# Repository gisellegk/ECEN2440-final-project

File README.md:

# ECEN2440-final-project

## Setup
### Eagle
Add folder to project folders: `Options>Directories>Projects`: Add a semicolon after the default / whatever's in there already, then add `<yourfolderpath>\ECEN2440-final-project/PCB`

### CCS
Set workspace to be `<yourfolderpath>\ECEN2440-final-project`. Go to file > import >Code Composer Studio > CCS projects. Hit Browse next to the Select search directory line, and navigate to the ECEN 2440 final project. You should see `rocket-payload-code` show up. Make sure that's checked off, then hit finish.

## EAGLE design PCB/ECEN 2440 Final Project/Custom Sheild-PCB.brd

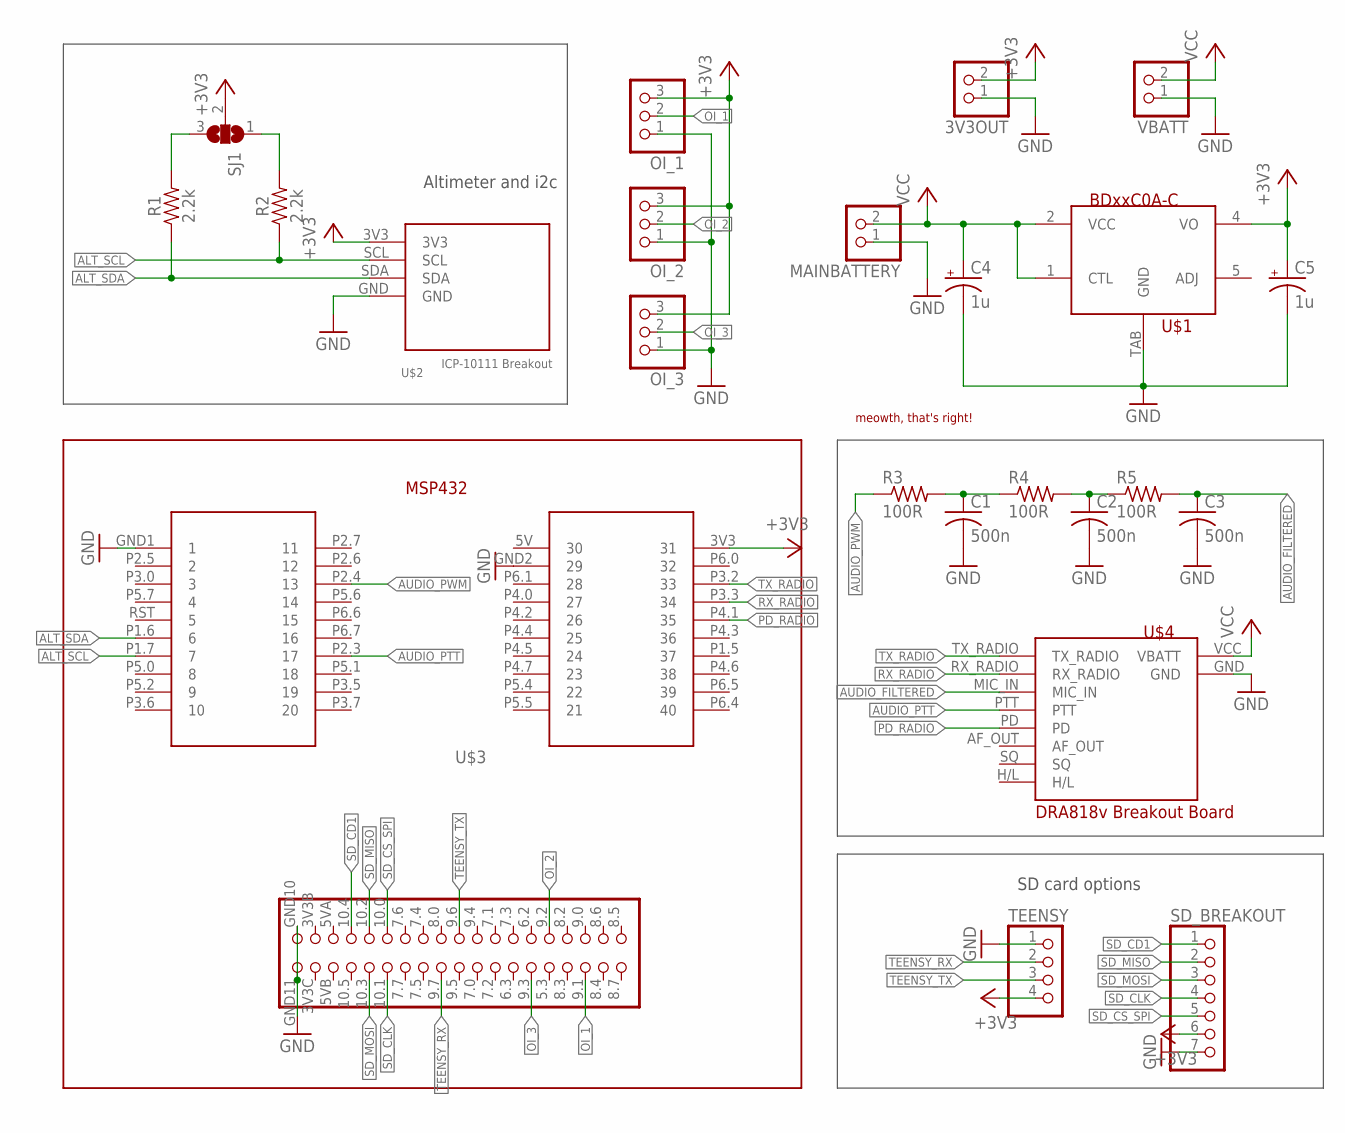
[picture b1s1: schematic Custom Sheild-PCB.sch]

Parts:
3V3OUT: PINHD-1X2; 1X02
C1, C2, C3: 500n; C0805
C4, C5: 1u; PANASONIC_A
MAINBATTERY: PINHD-1X2; 1X02
OI_1, OI_2, OI_3: PINHD-1X3; 1X03
R1, R2: 2.2k; 0603
R3, R4, R5: 100R; R0805
SD_BREAKOUT: PINHD-1X7; 1X07
SJ1: SJ2W; SJ_2
TEENSY: PINHD-1X4; 1X04
U$1: BDXXC0A-CBD33C0AWFP-CE2; TO252-5-11
U$2: ALTIMETER
U$3: MSP432
U$4: DRA_BREAKOUT
U$5: MEOWTH
VBATT: PINHD-1X2; 1X02

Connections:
30: U$3.5V (30)
+3V3: 3V3OUT.2, C5.+, OI_1.3, OI_2.3, OI_3.3, SD_BREAKOUT.6, SJ1.2, TEENSY.4, U$1.4 (VO), U$2.3V3, U$3.3V3 (31)
ALT_SCL: R2.1, U$2.SCL, U$3.P1.7 (7)
ALT_SDA: R1.1, U$2.SDA, U$3.P1.6 (6)
AUDIO_FILTERED: C3.1, R5.2, U$4.MIC_IN
AUDIO_PTT: U$3.P2.3 (17), U$4.PTT
AUDIO_PWM: R3.1, U$3.P2.4 (13)
GND: 3V3OUT.1, C1.2, C2.2, C3.2, C4.-, C5.-, MAINBATTERY.1, OI_1.1, OI_2.1, OI_3.1, SD_BREAKOUT.7, TEENSY.1, U$1.TAB (GND), U$2.GND, U$3.GND1 (1), U$3.GND2 (29), U$3.GND10 (42), U$3.GND11 (41), U$4.GND, VBATT.1
unnamed: R1.2, SJ1.3
unnamed: R2.2, SJ1.1
unnamed: C1.1, R3.2, R4.1
unnamed: C2.1, R4.2, R5.1
OI_1: OI_1.2, U$3.9.1 (73)
OI_2: OI_2.2, U$3.9.2 (70)
OI_3: OI_3.2, U$3.9.3 (67)
PD_RADIO: U$3.P4.1 (35), U$4.PD
RX_RADIO: U$3.P3.3 (34), U$4.RX_RADIO
SD_CD1: SD_BREAKOUT.1, U$3.10.4 (48)
SD_CLK: SD_BREAKOUT.4, U$3.10.1 (51)
SD_CS_SPI: SD_BREAKOUT.5, U$3.10.0 (52)
SD_MISO: SD_BREAKOUT.2, U$3.10.2 (50)
SD_MOSI: SD_BREAKOUT.3, U$3.10.3 (49)
TEENSY_RX: TEENSY.2, U$3.9.7 (57)
TEENSY_TX: TEENSY.3, U$3.9.6 (60)
TX_RADIO: U$3.P3.2 (33), U$4.TX_RADIO
VCC: C4.+, MAINBATTERY.2, U$1.1 (CTL), U$1.2 (VCC), U$4.VCC (VBATT), VBATT.2

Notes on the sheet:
Altimeter and i2c
SD card options

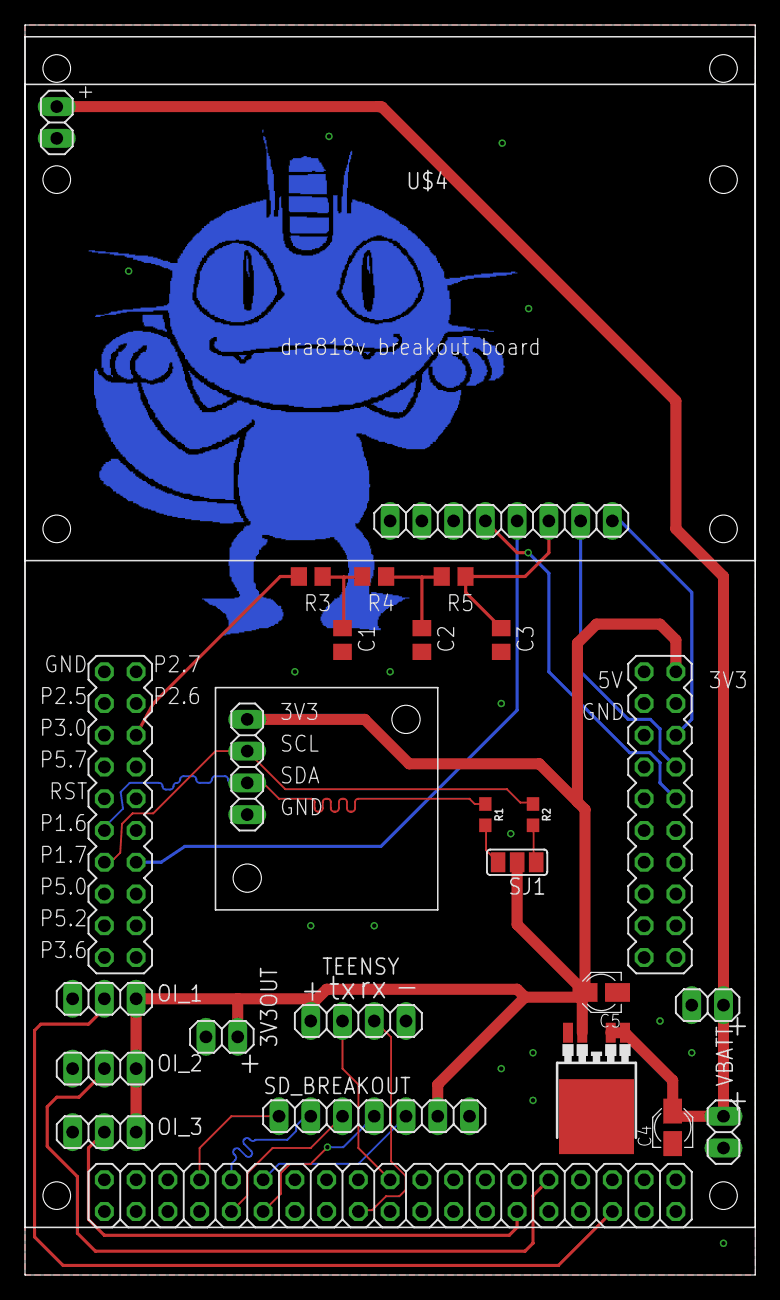
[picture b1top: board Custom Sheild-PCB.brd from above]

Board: 2 copper layers, 58.4 x 100.0 mm, 24 parts (1 on the bottom side), 25 nets.

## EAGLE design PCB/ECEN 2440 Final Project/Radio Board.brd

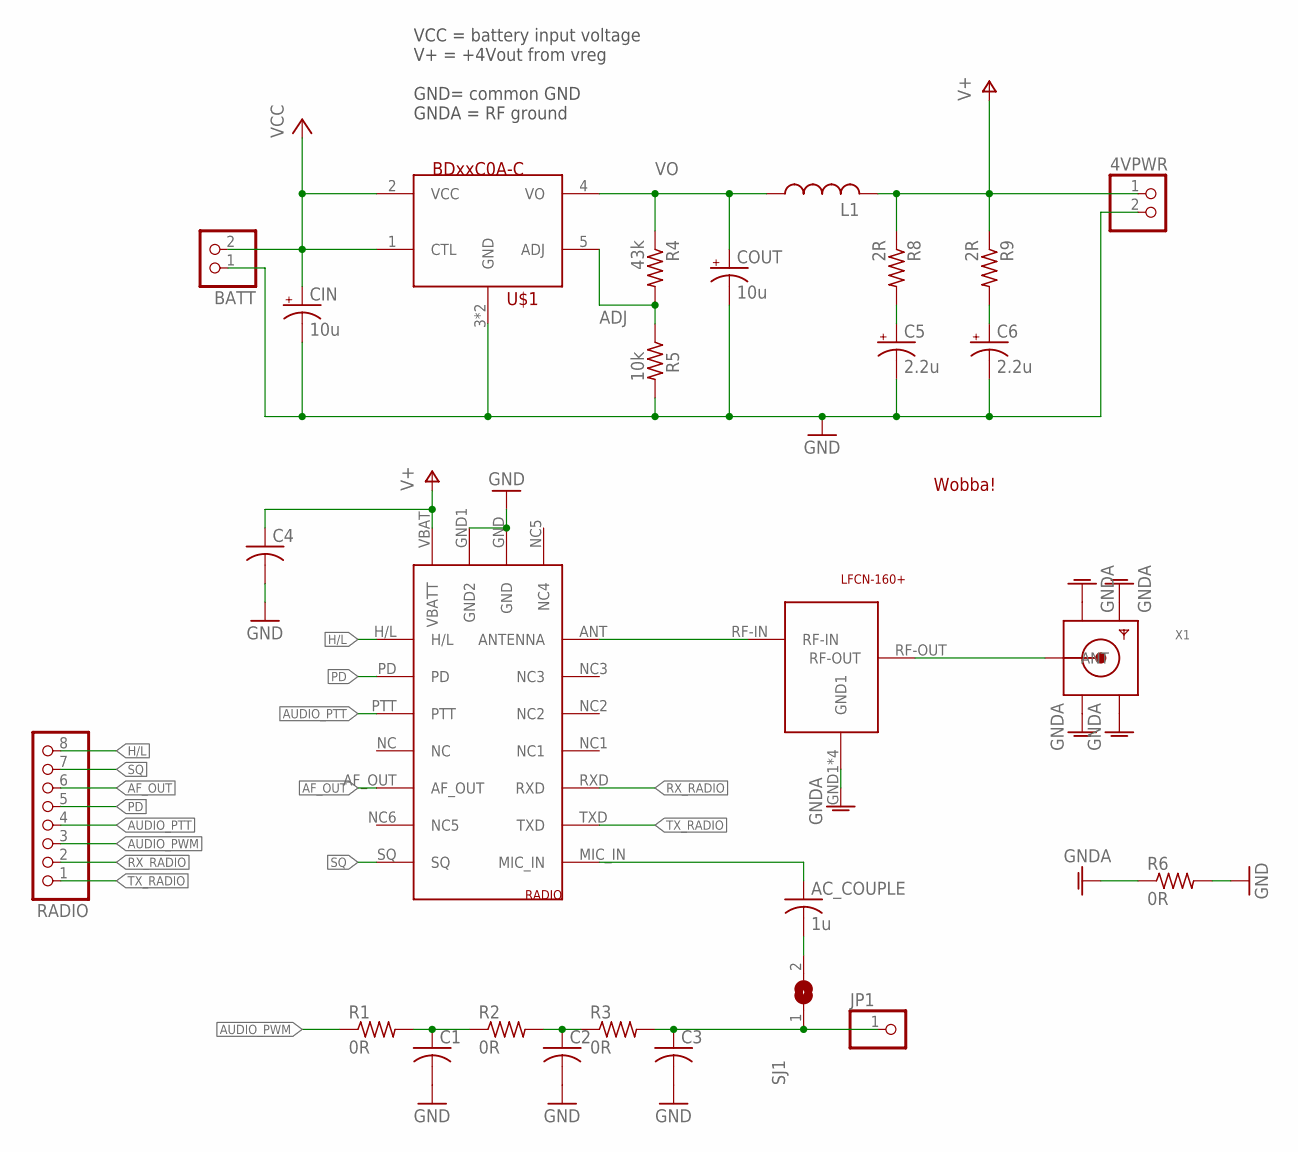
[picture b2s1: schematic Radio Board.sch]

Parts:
4VPWR: PINHD-1X2; 1X02
AC_COUPLE: 1u; C0805
BATT: PINHD-1X2; 1X02
C1, C2, C3: C-USC0805; C0805
C4: 100n; C0805
C5, C6: 2.2u; PANASONIC_A
CIN: 10u; PANASONIC_A
COUT: 10u; PANASONIC_A
JP1: PINHD-1X1; 1X01
L1: L-USL3225M; L3225M
R1, R2, R3, R6: 0R; R0805
R4: 43k; R0805
R5: 10k; R0805
R8, R9: 2R; R0805
RADIO: PINHD-1X8; 1X08
SJ1: SJ
U$1: BDXXC0A-CBD00C0AWHFP-CTR; HRP5
U$2: WOBBUFFET
U$4: RADIO
U$6: LFCN-160+
X1: SMACONNECTOR_EDGE; SMA_EDGELAUNCH

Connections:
ADJ: R4.2, R5.1, U$1.5 (ADJ)
AF_OUT: RADIO.6, U$4.AF_OUT
AUDIO_PTT: RADIO.4, U$4.PTT
AUDIO_PWM: R1.1, RADIO.3
GND: 4VPWR.2, BATT.1, C1.2, C2.2, C3.2, C4.2, C5.-, C6.-, CIN.-, COUT.-, R5.2, R6.2, U$1.3 (GND), U$1.6 (GND), U$4.GND, U$4.GND1 (GND2)
GNDA: R6.1, U$6.GND1, U$6.GND2 (GND1), U$6.P$1 (GND1), U$6.P$2 (GND1), X1.GND@1 (GND4), X1.GND@2 (GND3), X1.GND@3 (GND2), X1.GND@4 (GND1)
H/L: RADIO.8, U$4.H/L
unnamed: U$4.ANT (ANTENNA), U$6.RF-IN
unnamed: C1.1, R1.2, R2.1
unnamed: C3.1, JP1.1, R3.2, SJ1.1
unnamed: C2.1, R2.2, R3.1
unnamed: AC_COUPLE.1, U$4.MIC_IN
unnamed: U$6.RF-OUT, X1.P (ANT)
unnamed: AC_COUPLE.2, SJ1.2
unnamed: C6.+, R9.2
unnamed: C5.+, R8.2
PD: RADIO.5, U$4.PD
RX_RADIO: RADIO.2, U$4.RXD
SQ: RADIO.7, U$4.SQ
TX_RADIO: RADIO.1, U$4.TXD
V+: 4VPWR.1, C4.1, L1.2, R8.1, R9.1, U$4.VBAT (VBATT)
VCC: BATT.2, CIN.+, U$1.1 (CTL), U$1.2 (VCC)
VO: COUT.+, L1.1, R4.1, U$1.4 (VO)

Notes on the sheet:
VCC = battery input voltage V+ = +4Vout from vreg GND= common GND GNDA = RF ground

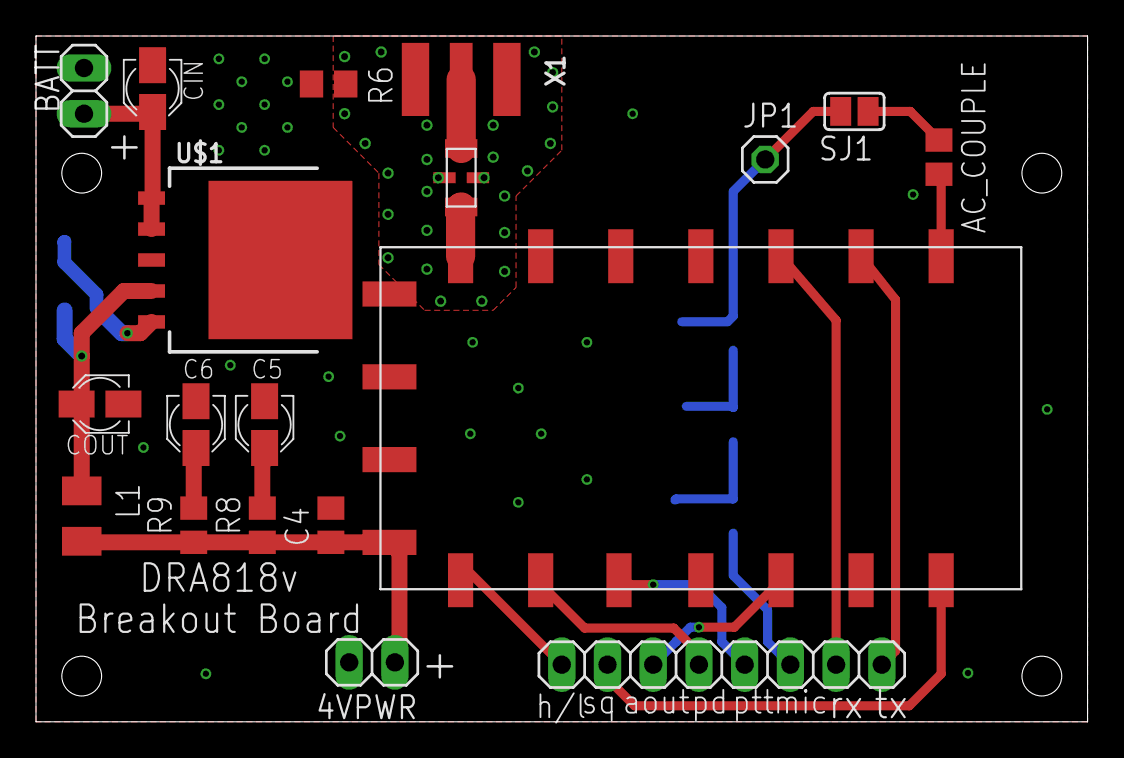
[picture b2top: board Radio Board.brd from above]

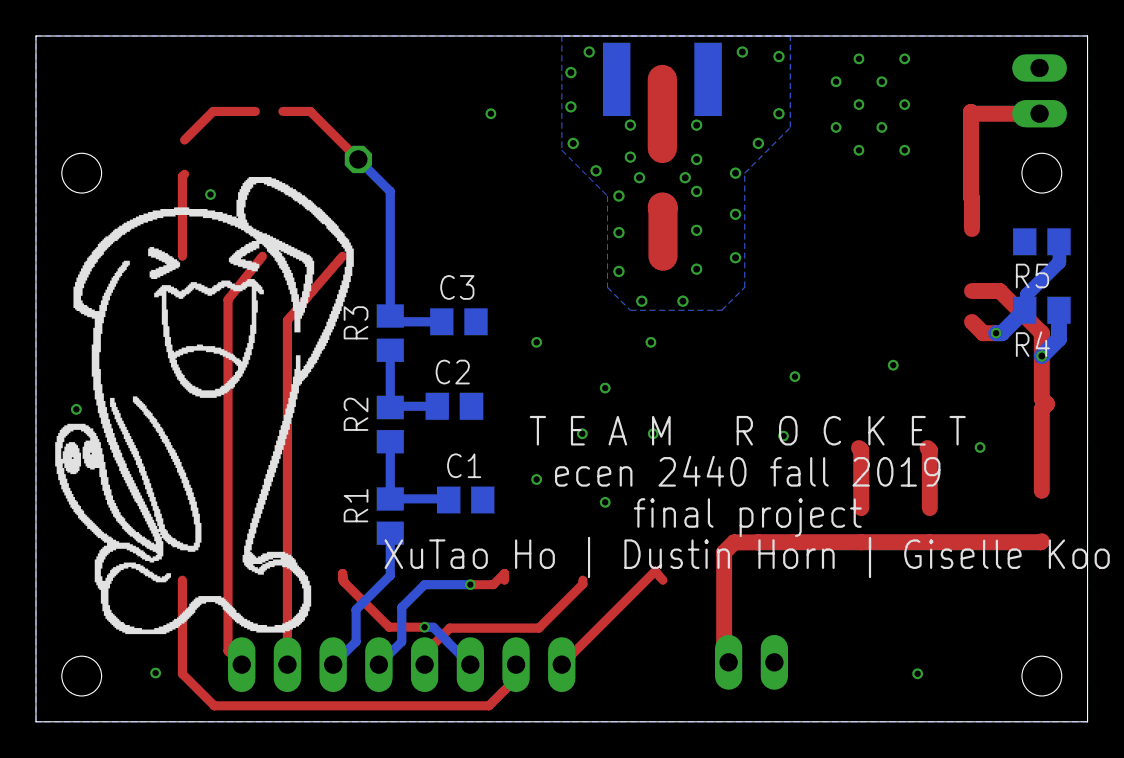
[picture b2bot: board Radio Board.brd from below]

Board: 2 copper layers, 58.4 x 38.1 mm, 28 parts (9 on the bottom side), 23 nets.

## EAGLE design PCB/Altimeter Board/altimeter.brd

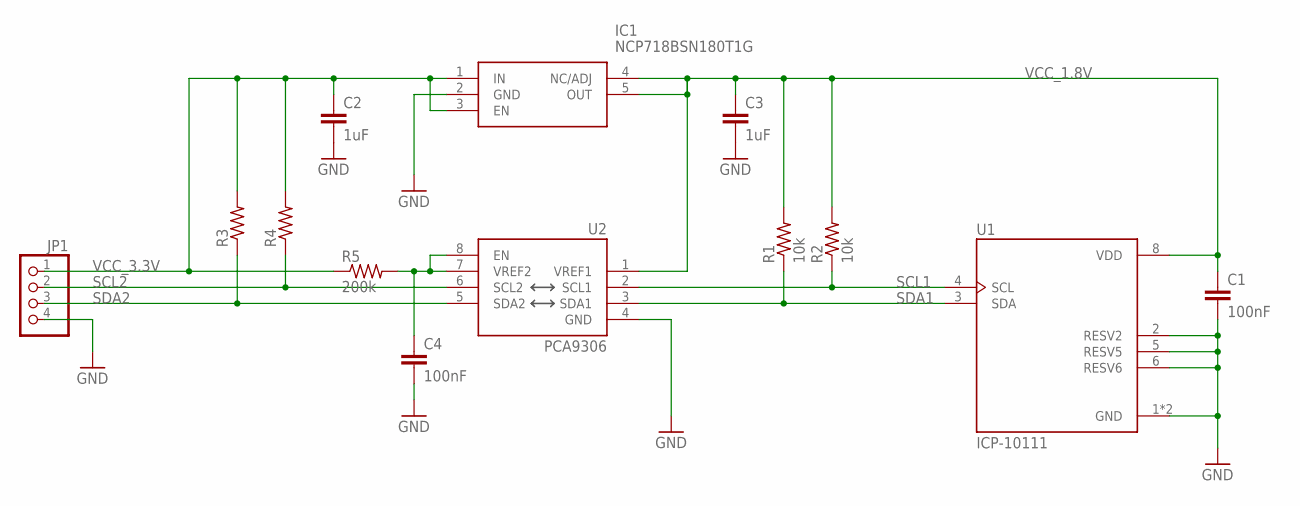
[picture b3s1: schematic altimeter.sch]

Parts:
C1, C4: 100nF; C0402
C2, C3: 1uF; C0402
IC1: NCP718BSN180T1G; SOT95P280X100-5N
JP1: PINHD-1X4; 1X04
R1, R2: 10k; R0402
R3, R4: R-US_R0402; R0402
R5: 200k; R0402
U1: ICP-10111; PSON65P250X200X100-8N
U2: PCA9306; PCA9306DC

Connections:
GND: C1.2, C2.2, C3.2, C4.2, IC1.2 (GND), JP1.4, U1.1 (GND), U1.2 (RESV2), U1.5 (RESV5), U1.6 (RESV6), U1.7 (GND), U2.4 (GND)
unnamed: C4.1, R5.2, U2.7 (VREF2), U2.8 (EN)
SCL1: R2.1, U1.4 (SCL), U2.2 (SCL1)
SCL2: JP1.2, R4.1, U2.6 (SCL2)
SDA1: R1.1, U1.3 (SDA), U2.3 (SDA1)
SDA2: JP1.3, R3.1, U2.5 (SDA2)
VCC_1.8V: C1.1, C3.1, IC1.4 (NC/ADJ), IC1.5 (OUT), R1.2, R2.2, U1.8 (VDD), U2.1 (VREF1)
VCC_3.3V: C2.1, IC1.1 (IN), IC1.3 (EN), JP1.1, R3.2, R4.2, R5.1

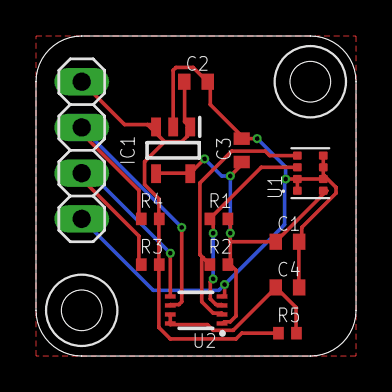
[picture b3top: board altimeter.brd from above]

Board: 2 copper layers, 17.8 x 17.8 mm, 15 parts (0 on the bottom side), 8 nets.

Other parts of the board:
U$1, U$2: #2

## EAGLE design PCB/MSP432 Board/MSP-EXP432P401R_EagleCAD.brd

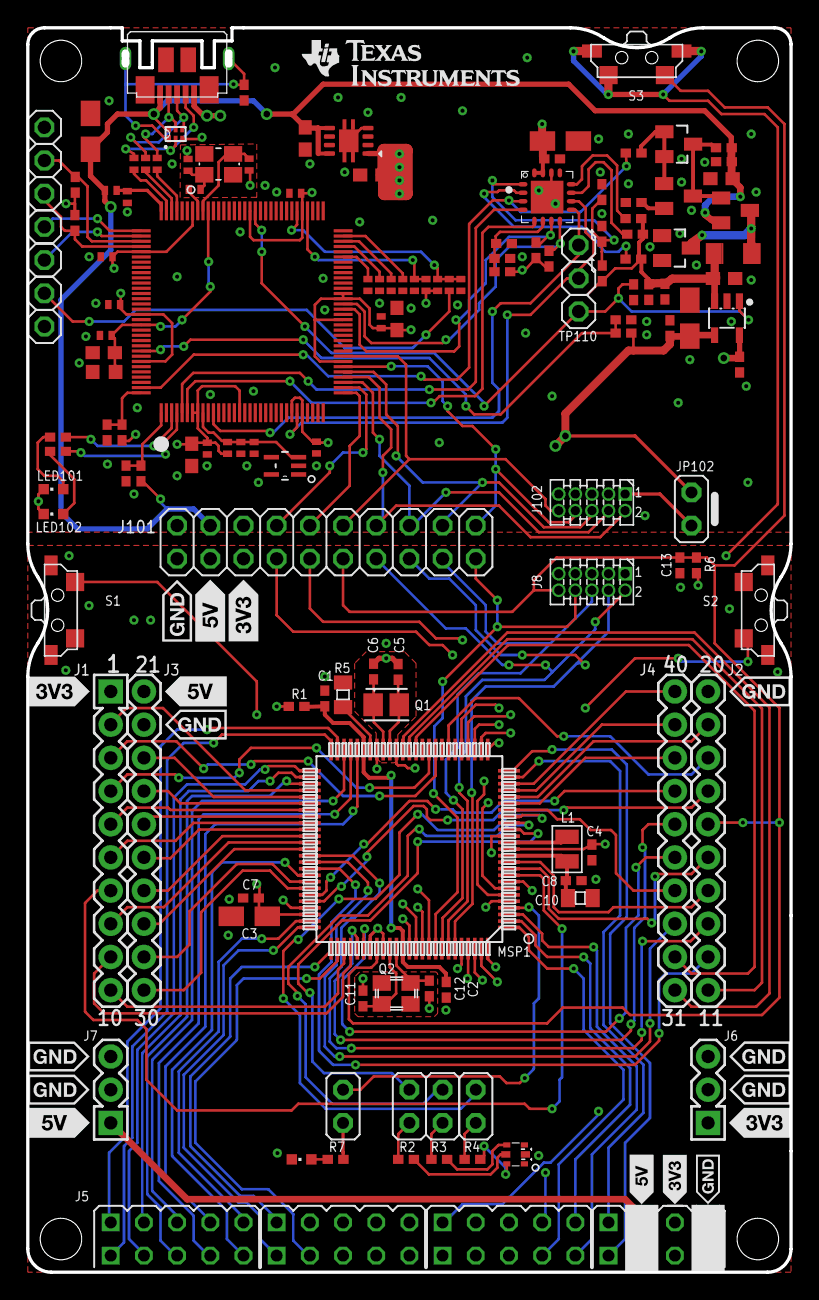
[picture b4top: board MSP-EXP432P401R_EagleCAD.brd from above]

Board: 4 copper layers, 58.1 x 94.9 mm, 150 parts (0 on the bottom side), 160 nets.

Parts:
C1, C2, C4, C7, C8, C118, C120, C124, C129: 100n; 0402
C3: 10u; A/3216-18R
C5, C6, C11, C12: 22p; 0402
C10: 4u7; CSMD0805
C13: 1n; 0402
C101, C102: 12pF; C0402
C103, C131, C150: 0.1uF; C0402
C104, C110, C112, C114, C123: 10n; C0402
C105: 2u2; C0603
C106, C140: 4.7u; A/3216-18R
C107, C130, C132, C141: 1u; C0603
C108: DNP; C0402
C111, C113, C121: 100n; C0402
C115, C116: 33p; 0402
C117, C119: 4.7u; C0603
C126, C127: 220n; 0402
C128: 47u; A/3216-18R
C133: 2.2uF; C0603K
D101, D102: BAS40-05; SOT23
IC101: TPS73533DRB; SON8
IC102: TPD4E004_DRY_6; DRY6
IC103: TPS2102DBV; SOT23-5
IC106: TM4C129ENCPDT; TQFP-128
IC107: LM4040B25_DCK_5; DCK5
J1: J1
J2: J2
J3: J3
J4: J4
J5: EDGE_CON; BOTTOM_CONNECTOR
J6: HEADER 1X03; 3PIN_PWR_3V3
J7: BP_HEADERS_PWR_5V; 3PIN_PWR_5V
J8, J102: ARM-10
J101: J101_432
JP8: LED1; JP1M
JP9: LED2_RED; JP1M
JP10: LED2_GREEN; JP1M
JP11: LED2_BLUE; JP1M
JP102: JP1M
L1: 4.7uH; 0806
L101: 2u2; L3216C
LED1, LED101, LED102: CHIPLED_0603
LED2: EVERLIGHT_19-337; RGB_LED
MSP1: MSP432; PZ100
MSP101: MSP430G2452IRSA16R; RSA16
Q1: LF_XTAL
Q2: FA-238
Q101: NX3225GA_OSC; NX3225GA
R1: 0R; 0402
R2: 110R; 0402
R3: 16R; 0402
R4: 24R; 0402
R5: 91kOhm, 0.1%, 25ppm/C; 0805
R6, R107: 47k; 0402
R7, R111, R120, R124: 470; 0402
R101, R134: DNP; 0402
R102: 100; R0402
R103: 10k; R0402
R104, R140: 51; R0402
R105: 1k 1%; R0402
R106: 2R; R0402
R108, R109, R110: 1k; R0402
R112, R113, R114, R115, R133, R135, R136: 220k; 0402
R116, R117: 4k7; 0402
R118: 820; 0402
R119: 0; 0402
R123: 33; 0402
R125, R129: 10k; 0402
R126: 2k2; 0402
R127: 3k3; 0402
R128: 6k8; 0402
R131, R137, R138: 0; R0402
R132: 330k; 0402
R139: dnp; R0402
S1, S2, S3: TS-1188E
T101: DMG1013UW; SOT23
T102: BC850CW-115; SOT23-BEC
TP101, TP102, TP103, TP104, TP105, TP106, TP107, TP108, TP109, TP110: TEST_PIN2; 1X01
U$1, U$2, U$3, U$5: MOUNTHOLE_125MIL
U$4: LOGO16_TPLACE
U$7: MIKE_TM
U$8: P401R_REARSILK_REV2_1
U$9: REAR_TILOGO
U$10: COMPLIANCE_SUITESYMBOLONLY; EVM_COMPLIANCESUITE_SYMBOLONLY
U$11: COMPLIANCE_FCC_TEXTREAR; COMPLIANCE_FCC_TEXT
U$12: LOGO-ROCKET
U$13: P401R_SILKLABEL; SILKLABELUPDATED
USB101: MOLEX_105164-0001

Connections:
!RST: C13.1, J2.16, J8.10, J101.11, MSP1.83, R6.1, S3.S1
+3V3: C3.+, C4.1, C7.1, J1.1, J5.35, J5.36, J6.1, J8.1, J101.5, MSP1.13, MSP1.73, R1.1, R6.2
+5V: J3.21, J5.33, J5.34, J7.1, J101.3
AVCC: C116.2, MSP101.6, R114.2, R115.1
AVCCOUT: C115.2, MSP101.1, R112.2, R113.1
DCDCCAL0: MSP101.12, R126.2
DCDCCAL1: MSP101.2, R127.2
DCDCCAL2: MSP101.11, R128.2
DCDCIO0: IC106.P$5, MSP101.4
DCDCIO1: IC106.P$6, MSP101.5
DCDCPULSE: IC106.P$127, MSP101.3, R118.2
DCDCRST: IC106.P$11, MSP101.9, TP108.1
DCDCTEST: IC106.P$27, MSP101.10, TP109.1
DCOR: MSP1.44, R5.1
HOSTSCL: IC106.P$49, MSP101.7, R117.2
HOSTSDA: IC106.P$50, MSP101.8, R116.2
IRSTN: R102.1, TP106.1
ITCK: IC106.P$100, R129.1, TP103.1
ITDI: IC106.P$98, TP105.1
ITDO: IC106.P$97, TP104.1
ITMS: IC106.P$99, R125.1, TP102.1
LED0: IC106.P$3, R111.1
LED1: IC106.P$4, R124.1
unnamed: J102.1, JP102.2
unnamed: IC106.P$63, R108.2
unnamed: LED102.A, R124.2
unnamed: C1.1, C2.1, MSP1.45, MSP1.87, R1.2
unnamed: LED101.A, R111.2
unnamed: JP9.2, R2.1
unnamed: LED2.5, R2.2
unnamed: LED2.6, R3.2
unnamed: LED2.4, R4.2
unnamed: R119.1, T102.E
unnamed: D101.1, D101.2, R118.1, T102.B
unnamed: D102.3, L101.1, T101.3
unnamed: D101.3, R120.2, T101.1, T102.C
unnamed: LED1.A, R7.2
unnamed: JP10.2, R3.1
unnamed: IC106.P$93, R138.2
unnamed: IC106.P$61, R110.2
unnamed: IC106.P$95, R131.2
unnamed: JP11.2, R4.1
unnamed: IC106.P$62, R109.2
unnamed: JP8.2, R7.1
unnamed: C6.1, MSP1.42, Q1.1
unnamed: C5.1, MSP1.41, Q1.2
unnamed: IC106.P$59, R139.2
OSC0: C102.1, IC106.P$88, Q101.3
OSC1: IC106.P$89, R106.2
OSC1_R: C101.1, Q101.1, R106.1
P1.0_LED1: JP8.1, MSP1.4
P1.1_BUTTON1: MSP1.5, S1.S1
P1.2_BCLUART_RXD: J101.7, MSP1.6
P1.3_BCLUART_TXD: J101.9, MSP1.7
P1.4_BUTTON2: MSP1.8, S2.S1
P1.5_SPICLK_J1.7: J1.7, MSP1.9
P1.6_SPIMOSI_J2.15: J2.15, MSP1.10
P1.7_SPIMISO_J2.14: J2.14, MSP1.11
P2.0_RGBLED_RED: JP9.1, MSP1.16
P2.1_RGBLED_GREEN: JP10.1, MSP1.17
P2.2_RGBLED_BLUE: JP11.1, MSP1.18
P2.3_IO_J4.34: J4.34, MSP1.19
P2.4_PWM_J4.38: J4.38, MSP1.20
P2.5_PWM_J2.19: J2.19, MSP1.21
P2.6_PWM_J4.39: J4.39, MSP1.22
P2.7_PWM_J4.40: J4.40, MSP1.23
P3.0_IO_J2.18: J2.18, MSP1.32
P3.2_URXD_J1.3: J1.3, MSP1.34
P3.3_UTXD_J1.4: J1.4, MSP1.35
P3.5_IO_J4.32: J4.32, MSP1.37
P3.6_IO_J2.11: J2.11, MSP1.38
P3.7_IO_J4.31: J4.31, MSP1.39
P4.0_A13_J3.24: J3.24, MSP1.56
P4.1_IO_J1.5: J1.5, MSP1.57
P4.2_A11_J3.25: J3.25, MSP1.58
P4.3_A10_J1.6: J1.6, MSP1.59
P4.4_A9_J3.26: J3.26, MSP1.60
P4.5_A8_J3.27: J3.27, MSP1.61
P4.6_IO_J1.8: J1.8, MSP1.62
P4.7_A6_J3.28: J3.28, MSP1.63
P5.0_IO_J2.13: J2.13, MSP1.64
P5.1_IO_J4.33: J4.33, MSP1.65
P5.2/XT2IN: C12.1, MSP1.86, Q2.1
P5.2_IO_J2.12: J2.12, MSP1.66
P5.3: J5.9, MSP1.67
P5.3/XT2OUT: C11.1, MSP1.85, Q2.3
P5.4_IO_J3.29: J3.29, MSP1.68
P5.5_IO_J3.30: J3.30, MSP1.69
P5.6_PWM_J4.37: J4.37, MSP1.70
P5.7_IO_J2.17: J2.17, MSP1.71
P6.0_A15_J1.2: J1.2, MSP1.54
P6.1_A14_J3.23: J3.23, MSP1.55
P6.2: J5.12, MSP1.76
P6.3: J5.13, MSP1.77
P6.4_I2CSDA_J1.10: J1.10, MSP1.78
P6.5_I2CSCL_J1.9: J1.9, MSP1.79
P6.6_CAPTURE_J4.36: J4.36, MSP1.80
P6.7_CAPTURE_J4.35: J4.35, MSP1.81
P7.0: J5.17, MSP1.88
P7.1: J5.16, MSP1.89
P7.2: J5.15, MSP1.90
P7.3: J5.14, MSP1.91
P7.4: J5.24, MSP1.26
P7.5: J5.23, MSP1.27
P7.6: J5.26, MSP1.28
P7.7: J5.25, MSP1.29
P8.0: J5.22, MSP1.30
P8.2: J5.8, MSP1.46
P8.3: J5.7, MSP1.47
P8.4: J5.6, MSP1.48
P8.5: J5.2, MSP1.49
P8.6: J5.1, MSP1.50
P8.7: J5.3, MSP1.51
P9.0: J5.4, MSP1.52
P9.1: J5.5, MSP1.53
P9.2: J5.10, MSP1.74
P9.3: J5.11, MSP1.75
P9.4: J5.18, MSP1.96
P9.5: J5.19, MSP1.97
P9.6: J5.20, MSP1.98
P9.7: J5.21, MSP1.99
P10.0: J5.28, MSP1.100
P10.1: J5.27, MSP1.1
P10.2: J5.30, MSP1.2
P10.3: J5.29, MSP1.3
P10.4: J5.32, MSP1.24
P10.5: J5.31, MSP1.25
P96VBUS: C150.1, IC106.P$96, R140.2
REF_MAIN_LDO: IC106.P$128, R135.2, R136.2
REF_TARGET_VCC: IC106.P$120, R101.2, R134.2
TCK_SWDCLK: J8.4, J101.15, MSP1.95
TDI: J8.8, J101.19, MSP1.92
TDO_SWO: J8.6, J101.17, MSP1.93
TMS_SWDIO: J8.2, J101.13, MSP1.94
VBUS_DETECT: IC106.P$1, R132.2, R133.2
VCCEN1: IC103.1, IC106.P$78, R107.1, TP110.1
VCORE: C8.1, C10.1, L1.1, MSP1.12
VDDC: C131.1, C132.2, C133.1, IC106.P$87, IC106.P$115
VREFA+: C110.1, C111.1, IC106.P$9, IC107.3, R105.1
VSW: L1.2, MSP1.14
XDS-GND: C1.2, C2.2, C3.-, C4.2, C5.2, C6.2, C7.2, C8.2, C10.2, C11.2, C12.2, C13.2, J2.20, J3.22, J5.37, J5.38, J6.2, J6.3, J7.2, J7.3, J8.3, J8.5, J8.7, J8.9, J101.1, LED1.C, LED2.1, LED2.2, LED2.3, MSP1.15, MSP1.40, MSP1.43, MSP1.72, MSP1.82, MSP1.84, R5.2, S1.G1, S1.G2, S1.S2, S2.G1, S2.G2, S2.S2, S3.G1, S3.G2, S3.S2
XDSET_!RST: C108.1, IC106.P$70, R102.2, R103.2
XDSET_DM: IC102.5, R138.1, USB101.D-
XDSET_DP: IC102.4, R137.1, USB101.D+
XDSET_DPR: IC106.P$94, R137.2
XDSET_GND: C101.2, C102.2, C103.2, C104.2, C105.2, C106.-, C107.2, C108.2, C110.2, C111.2, C112.2, C113.2, C114.2, C115.1, C116.1, C117.2, C118.2, C119.2, C120.2, C121.2, C123.2, C124.2, C126.2, C127.2, C128.-, C129.2, C130.1, C131.2, C132.1, C133.2, C140.-, C141.2, C150.2, D102.1, D102.2, IC101.4, IC101.9, IC102.3, IC103.2, IC106.P$10, IC106.P$17, IC106.P$48, IC106.P$55, IC106.P$58, IC106.P$64, IC106.P$66, IC106.P$80, IC106.P$114, IC107.1, J101.2, J102.3, J102.5, J102.7, J102.9, LED101.C, LED102.C, MSP101.13, MSP101.14, MSP101.TP, R101.1, R107.2, R108.1, R109.1, R110.1, R113.2, R115.2, R119.2, R123.2, R133.1, R136.1, R139.1, TP101.1, USB101.GND
XDSET_ID: IC102.2, R131.1, USB101.ID
XDSET_RESET_OUT: IC106.P$40, J101.12, J102.10
XDSET_RXD: IC106.P$33, J101.10
XDSET_SHIELD: IC102.1, R123.1, USB101.SHIELD_TH1, USB101.SHIELD_TH2
XDSET_TCK_SWDCLK: IC106.P$35, J101.16, J102.4
XDSET_TDI: IC106.P$38, J101.20, J102.8
XDSET_TDO_SWO: IC106.P$37, J101.18, J102.6
XDSET_TMS_SWDIO: IC106.P$36, J101.14, J102.2
XDSET_TXD: IC106.P$34, J101.8
XDSET_VBAT: C103.1, IC106.P$68, R104.2
XDSET_VBUS: C117.1, C118.1, C140.+, C141.1, IC101.5, IC101.8, IC102.6, J101.4, R120.1, R132.1, R140.1, T101.2, USB101.VBUS
XDSET_VCC: C104.1, C105.1, C106.+, C107.1, C112.1, C113.1, C114.1, C121.1, C123.1, C124.1, C126.1, C130.2, IC101.1, IC103.5, IC106.P$7, IC106.P$8, IC106.P$16, IC106.P$26, IC106.P$28, IC106.P$39, IC106.P$47, IC106.P$51, IC106.P$52, IC106.P$69, IC106.P$79, IC106.P$90, IC106.P$101, IC106.P$113, IC106.P$122, MSP101.15, MSP101.16, R103.1, R104.1, R105.2, R114.1, R116.1, R117.1, R125.2, R129.2, R135.1, TP107.1
XDSET_VCCOUT: C119.1, C120.1, C127.1, IC103.3, L101.2, R112.1, R126.1, R127.1, R128.1
XDSET_VCCTARGET: C128.+, C129.1, IC103.4, J101.6, JP102.1, R134.1

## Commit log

2019-10-30 setting up folder structure
2019-10-30 add ccs project folder
2019-10-30 added comment
2019-10-30 add readme with setup instructions for eagle and CCS
2019-10-30 markdown syntax
2019-11-06 final project proposal commit
2019-11-11 Add PCB stuff with components and a couple wiring traces
2019-11-11 add ltspice files and screenshots
2019-11-11 ltspice
2019-11-11 Created Library
2019-11-11 add altimeter board
2019-11-11 Created library and made altimeter
2019-11-12 Made MSP432 and fixed other components
2019-11-13 Added the radio device, and made a couple connections
2019-11-13 Fixed the DRA818 and started connecting traces
2019-11-13 Made changes to the MSP432 and added bottom row
2019-11-13 made a couple connections
2019-11-14 Connected Pins
2019-11-14 add teensy lib
2019-11-14 Work
2019-11-14 PDR schematic and board
2019-11-14 Final board and schematic
2019-11-15 Made updates to board and created now radio breakout board
2019-11-17 add unnecessary files to gitignore
2019-11-17 add some new ltpsice models
2019-11-17 add pcb way quote image
2019-11-17 lt spice stuff
2019-11-17 Revision 1 of Altimeter code
2019-11-18 add preliminary teensy UART stuff
2019-11-18 Altimeter Code Revision 3 (in Altimeter Rev. 2 Folder)
2019-11-18 add uart WIP stuff from lab folder
2019-11-18 minor changes to board
2019-11-18 Board
2019-11-18 move teensy code into code dir
2019-11-18 mod gitignore
2019-11-18 move code into code directory
2019-11-18 New changes to pcb board
2019-11-18 Final updates to the board
2019-11-18 remove files i accidentally forgot to gitignore
2019-11-18 gitignore those files
2019-11-19 add altimeter test code & screenshot
2019-11-19 i forgot it was a git repo inside T_T
2019-11-19 radio board routing
2019-11-19 PWM Code and Computations
2019-11-19 final (before review & order) dra818v breakout board
2019-11-19 prettyfy schematic. vague shield board layout.
2019-11-19 I2C Code for Altimeter
2019-11-20 Changes to board of sheild
2019-11-20 changes to the sheild board
2019-11-20 changes to the traces of the shield board
2019-11-20 changes to the traces of the sheild board
2019-11-20 changes to traces on sheild board
2019-11-22 Created PWM code and did stuff with code
2019-11-22 SPICE models everywhere
2019-11-23 final (i hope) radio board
2019-11-24 final board maybe??
2019-11-24 pspice is terrible
2019-11-24 naming
2019-11-24 add voltage test points
2019-11-24 Fix MSP432 footprint
2019-11-25 really important commit
2019-11-25 idk what i changed lol
2019-11-27 UART echoing works
2019-11-27 update gitignore to reflect new file structure.
2019-11-27 i wonder if we should just gitignore the .epf file
2019-11-27 successfully prints garbage (i mean, randomly generated letters) over UART.
2019-11-27 a bit more abstracted
2019-11-27 teensy uart tested and works
2019-11-27 it does a thing
2019-11-29 worked on PWM code
2019-11-29 Housing for the Rocket
2019-11-29 Changes to housing
2019-11-29 worked on pwm code, still errors on float type
2019-11-30 I2C and PWM
2019-11-30 Global Variable PWM Change
2019-11-30 code PWM
2019-12-01 update gitignore
2019-12-01 update pspice files
2019-12-01 add ltspice files
2019-12-01 final board stuff
2019-12-01 PWM: add while(1) loop, modulus for the array, fix indentation?
2019-12-01 create folder for Morse Code Keyer code
2019-12-02 abstract altimeter data requests
2019-12-02 starting code integration for SD and alt
2019-12-02 uart SD logging + altimeter
2019-12-03 ADDED example code
2019-12-03 Update morse code and teensy
2019-12-03 Teensy acknowledge
2019-12-04 Changes to the Housing
2019-12-04 teensy sd + alt
2019-12-04 STL files
2019-12-05 expand logging capabilities
2019-12-05 Calibration Code
2019-12-05 uart + alt
2019-12-05 asdf
2019-12-06 Lots of changes during Thursday Hell
2019-12-06 why is uart being weird
2019-12-06 one commit to rule them all
2019-12-06 data
2019-12-06 Cap housing
2019-12-06 Cap changes housing
2019-12-07 CAP changes
2019-12-07 morse code
2019-12-07 Final Countdown
2019-12-07 teensy hack fix
2019-12-07 better teensy uart hack
2019-12-07 add new file code. for some reason correct indexing broke

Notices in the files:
PCB/MSP432 Board/MSP-EXP432P401R_EagleCAD.brd:
(C)2003 A. DANNENBERG
parts and their libraries:
SparkFun-IC-Comms: Licensing: Creative Commons ShareAlike 4.0 International - https://creativecommons.org/licenses/by-sa/4.0
